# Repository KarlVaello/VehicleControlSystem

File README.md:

# Vehicle Control System

### What is VCS?
In modern vehicles almost 80% of the vehicle is controlled electronically. That's just VCS, a control system. Focused on electric vehicles but can be easily modified for other types.
VCS consists of several units and modules, all connected by an area network bus, based on rs-485 and my own [data protocol](https://github.com/KarlVaello/VCS/wiki/Unit-Communication-protocol), allowing modularization.
In this project you will find both the hardware and the software of each unit or module.

 Electronic control units / modules
 
UNITS:
- CCU Central Control Unit
	- CCU Cluster Control Unit
	- CCU Central Control Unit
- EmCU Electric-motor Control Unit
- BCU Battery Control Unit

MODULES:
- CcCM Central-console Control Module
- SteeringWheel Control Module
- BCM Body Control Module
- BlCM Back-lights Control Module
- FlCM Front-lights Control Module

### SCREENSHOTS

BASE MODULE

# Full Documentation

See the [WIKI](https://github.com/KarlVaello/VCS/wiki) for full documentation, examples, operational details and other information.

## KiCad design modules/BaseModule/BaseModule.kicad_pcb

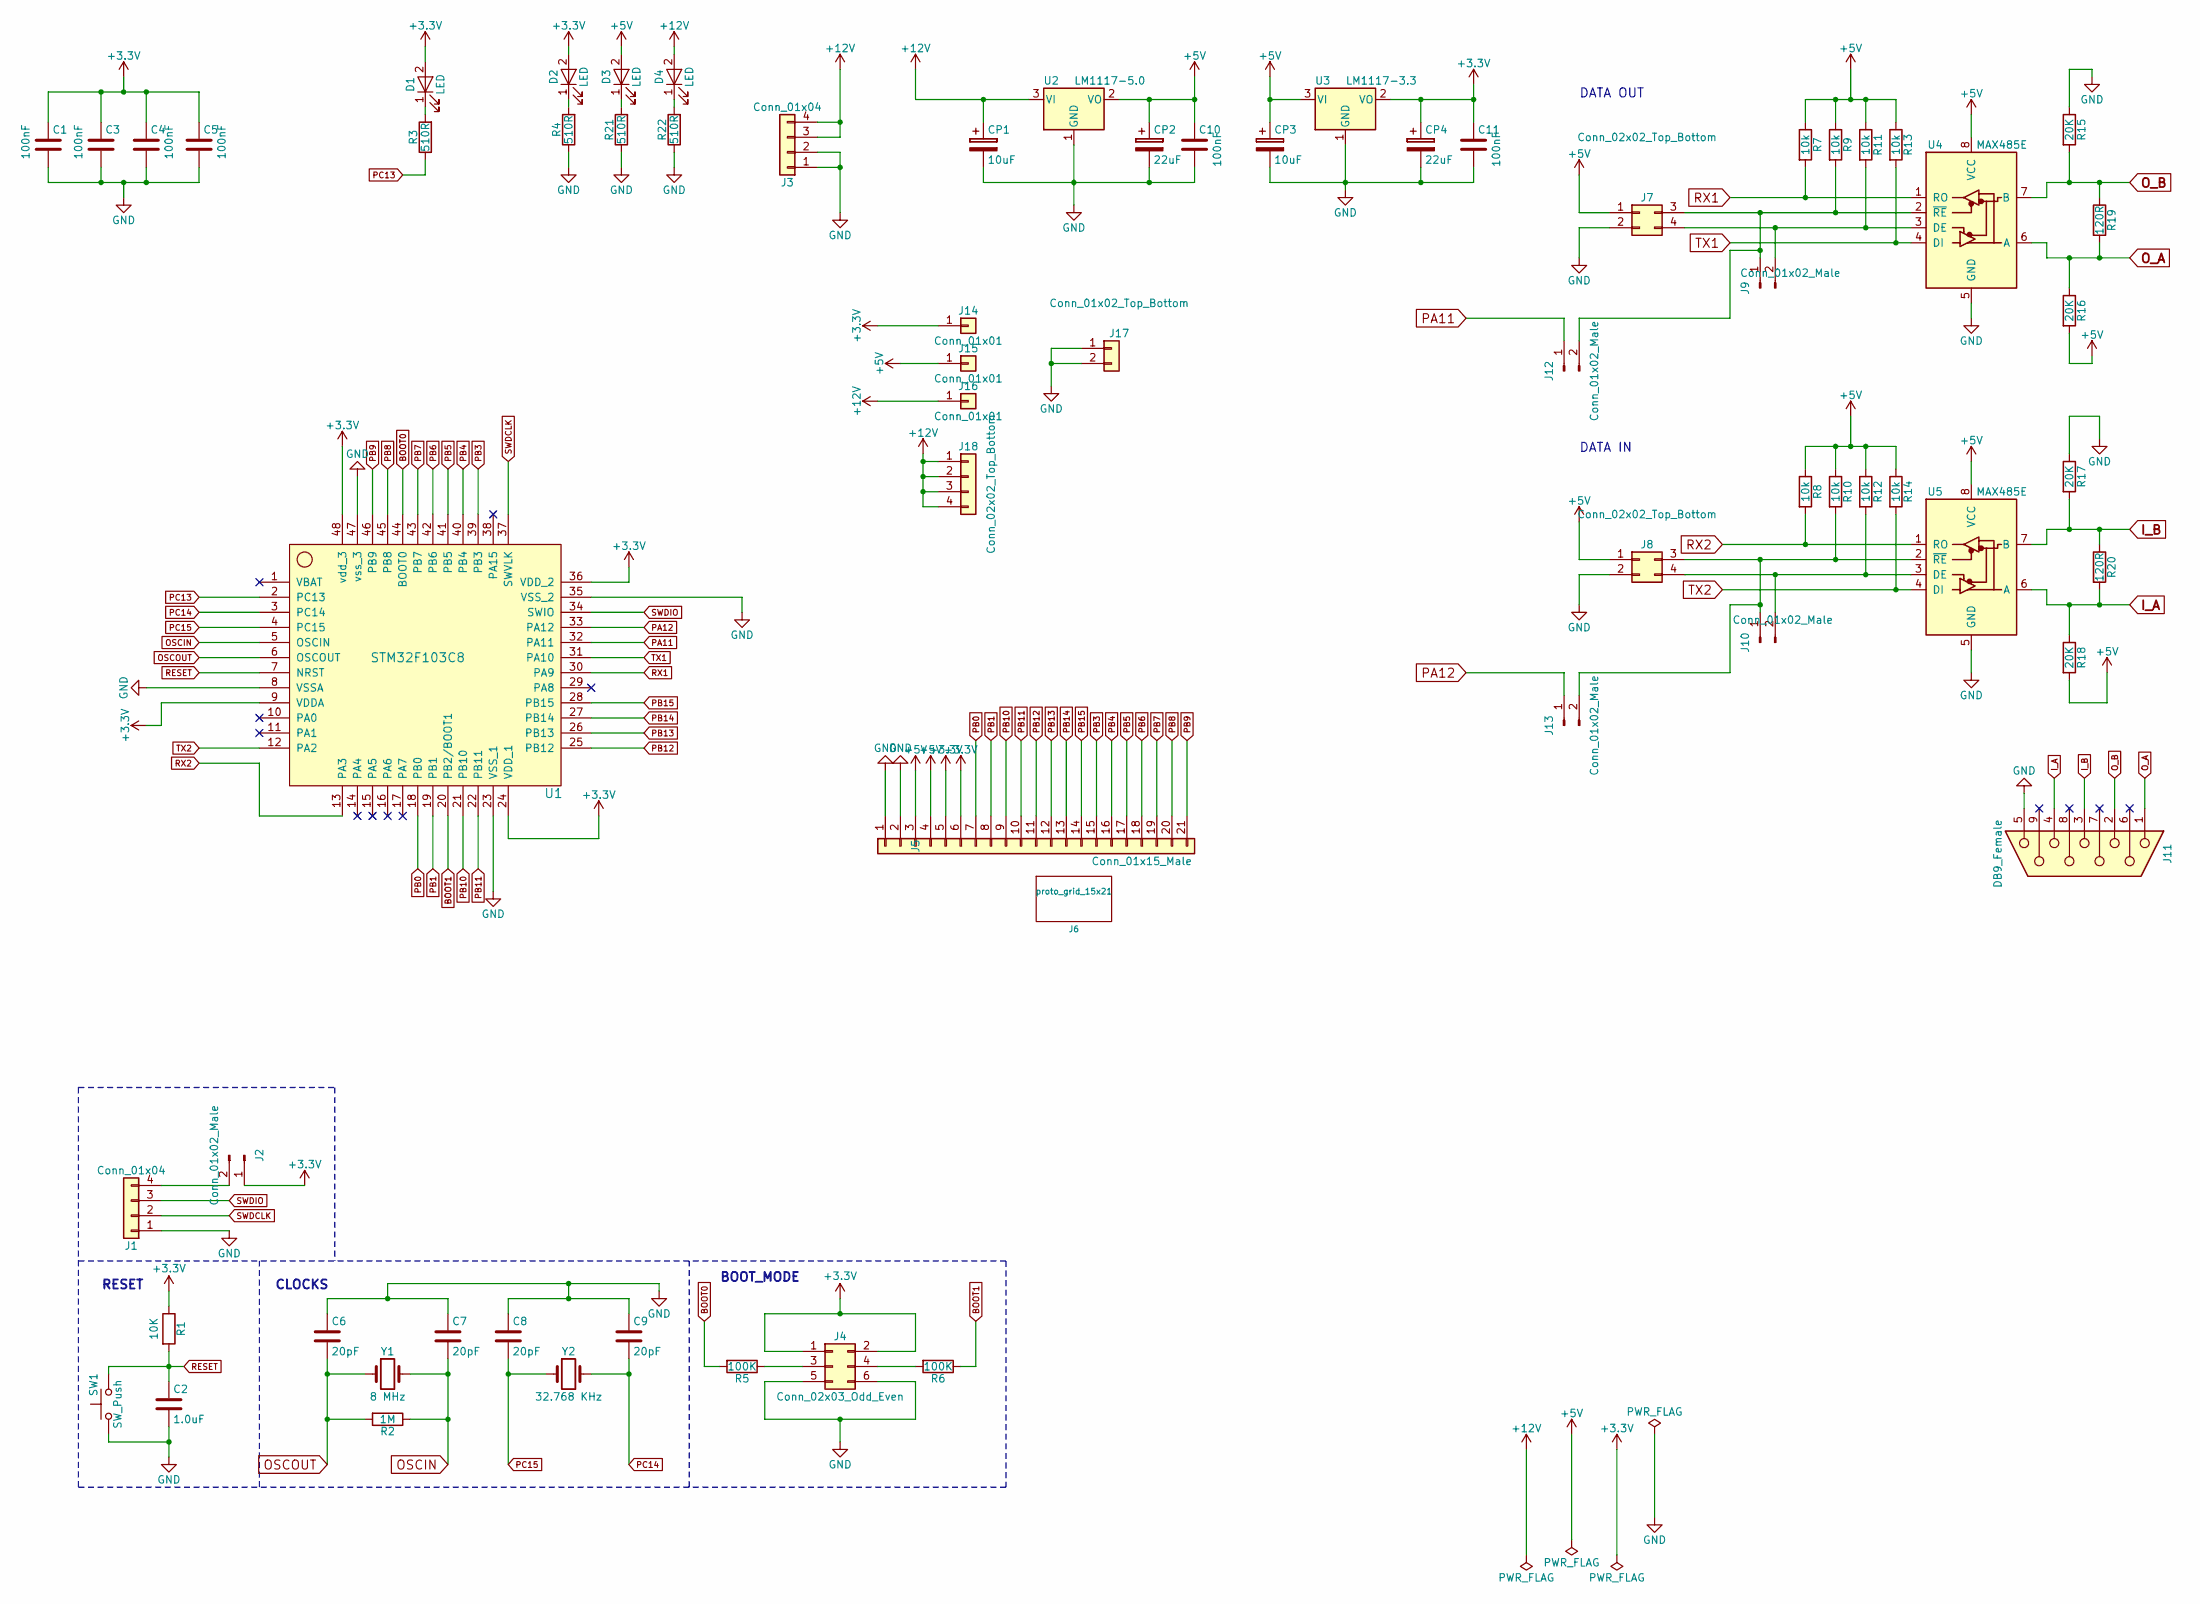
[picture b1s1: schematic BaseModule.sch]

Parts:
C1, C3, C4, C5: 100nF; C_0603_HandSoldering
C2: 1.0uF; C_0603_HandSoldering
C6, C7, C8, C9: 20pF; C_0603_HandSoldering
C10, C11: 100nF; C_0805_HandSoldering
CP1, CP3: 10uF; CP_Tantalum_Case-B_EIA-3528-21_Hand
CP2, CP4: 22uF; CP_Tantalum_Case-B_EIA-3528-21_Hand
D1, D2, D3, D4: LED; LED_0805_HandSoldering
J1: Conn_01x04; Pin_Header_Straight_1x04_Pitch2.54mm
J2, J9, J10, J12, J13: Conn_01x02_Male; Pin_Header_Straight_1x02_Pitch2.54mm
J3: Conn_01x04; Molex_MiniFit-JR-5569-04A2_2x02x4.20mm_Angled
J4: Conn_02x03_Odd_Even; Pin_Header_Straight_2x03_Pitch2.54mm
J5: Conn_01x15_Male; Socket_Strip_Straight_1x21_Pitch2.54mm
J6: proto_grid_15x21; grid
J7, J8: Conn_02x02_Top_Bottom; Pin_Header_Straight_2x02_Pitch2.54mm
J11: DB9_Female
J14, J15, J16: Conn_01x01; Pin_Header_Straight_1x01_Pitch2.54mm
J17: Conn_01x02_Top_Bottom; Pin_Header_Straight_1x02_Pitch2.54mm
J18: Conn_02x02_Top_Bottom; Socket_Strip_Straight_1x04_Pitch2.54mm
R1: 10K; R_0603_HandSoldering
R2: 1M; R_0603_HandSoldering
R3, R4, R21, R22: 510R; R_0603_HandSoldering
R5, R6: 100K; R_0603_HandSoldering
R7, R8, R9, R10, R11, R12, R13, R14: 10k; R_0603_HandSoldering
R15, R16, R17, R18: 20K; R_0603_HandSoldering
R19, R20: 120R; R_0603_HandSoldering
SW1: SW_Push; SW_PUSH_6mm_h8.5mm
U1: STM32F103C8; LQFP-48_7x7mm_Pitch0.5mm
U2: LM1117-5.0; SOT-223
U3: LM1117-3.3; SOT-223
U4, U5: MAX485E; SOIC-8_3.9x4.9mm_Pitch1.27mm
Y1: 8 MHz; Crystal_HC49-4H_Vertical
Y2: 32.768 KHz; Crystal_SMD_SeikoEpson_MC306-4pin_8.0x3.2mm_HandSoldering

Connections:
+3V3: C1.1, C3.1, C4.1, C5.1, C11.1, CP4.1, D1.2 (A), D2.2 (A), J2.1, J4.1, J4.2, J5.5, J5.6, J14.1, R1.1, U1.9 (VDDA), U1.24 (VDD_1), U1.36 (VDD_2), U1.48 (vdd_3), U3.2 (VO)
+5V: C10.1, CP2.1, CP3.1, D3.2 (A), J5.3, J5.4, J7.1, J8.1, J15.1, R7.1, R8.1, R9.1, R10.1, R11.1, R12.1, R13.1, R14.1, R16.2, R18.2, U2.2 (VO), U3.3 (VI), U4.8 (VCC), U5.8 (VCC)
+12V: CP1.1, D4.2 (A), J3.3, J3.4, J16.1, J18.1, J18.2, J18.3, J18.4, U2.3 (VI)
BOOT0: R5.2, U1.44 (BOOT0)
BOOT1: R6.1, U1.20 (PB2/BOOT1)
GND: C1.2, C2.2, C3.2, C4.2, C5.2, C6.1, C7.1, C8.1, C9.1, C10.2, C11.2, CP1.2, CP2.2, CP3.2, CP4.2, J1.1, J3.1, J3.2, J4.5, J4.6, J5.1, J5.2, J7.2, J8.2, J11.5, J17.1, J17.2, R4.1, R15.1, R17.1, R21.1, R22.1, SW1.1, U1.8 (VSSA), U1.23 (VSS_1), U1.35 (VSS_2), U1.47 (vss_3), U2.1 (GND), U3.1 (GND), U4.5 (GND), U5.5 (GND)
I_A: J11.4, R18.1, R20.2, U5.6 (A)
I_B: J11.3, R17.2, R20.1, U5.7 (B)
unnamed: D1.1 (K), R3.2
unnamed: D2.1 (K), R4.2
unnamed: D3.1 (K), R21.2
unnamed: D4.1 (K), R22.2
unnamed: J1.4, J2.2
unnamed: J4.3, R5.1
unnamed: J4.4, R6.2
unnamed: J7.4, J9.2, R11.2, U4.3 (DE)
unnamed: J8.3, J10.1, J13.2, R10.2, U5.2 (~RE)
unnamed: J8.4, J10.2, R12.2, U5.3 (DE)
unnamed: J7.3, J9.1, J12.2, R9.2, U4.2 (~RE)
OSCIN: C7.2, R2.1, U1.5 (OSCIN), Y1.2
OSCOUT: C6.2, R2.2, U1.6 (OSCOUT), Y1.1
O_A: J11.1, R16.1, R19.2, U4.6 (A)
O_B: J11.2, R15.2, R19.1, U4.7 (B)
PA11: J12.1, U1.32 (PA11)
PA12: J13.1, U1.33 (PA12)
PB0: J5.7, U1.18 (PB0)
PB1: J5.8, U1.19 (PB1)
PB3: J5.15, U1.39 (PB3)
PB4: J5.16, U1.40 (PB4)
PB5: J5.17, U1.41 (PB5)
PB6: J5.18, U1.42 (PB6)
PB7: J5.19, U1.43 (PB7)
PB8: J5.20, U1.45 (PB8~)
PB9: J5.21, U1.46 (PB9)
PB10: J5.9, U1.21 (PB10)
PB11: J5.10, U1.22 (PB11)
PB12: J5.11, U1.25 (PB12)
PB13: J5.12, U1.26 (PB13)
PB14: J5.13, U1.27 (PB14)
PB15: J5.14, U1.28 (PB15)
PC13: R3.1, U1.2 (PC13)
PC14: C9.2, U1.3 (PC14), Y2.2
PC15: C8.2, U1.4 (PC15), Y2.1
RESET: C2.1, R1.2, SW1.2, U1.7 (NRST)
RX1: R7.2, U1.30 (PA9), U4.1 (RO)
RX2: R8.2, U1.13 (PA3), U5.1 (RO)
SWDCLK: J1.2, U1.37 (SWVLK)
SWDIO: J1.3, U1.34 (SWIO)
TX1: R13.2, U1.31 (PA10), U4.4 (DI)
TX2: R14.2, U1.12 (PA2), U5.4 (DI)

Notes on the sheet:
DATA OUT
DATA IN
RESET
CLOCKS
BOOT_MODE

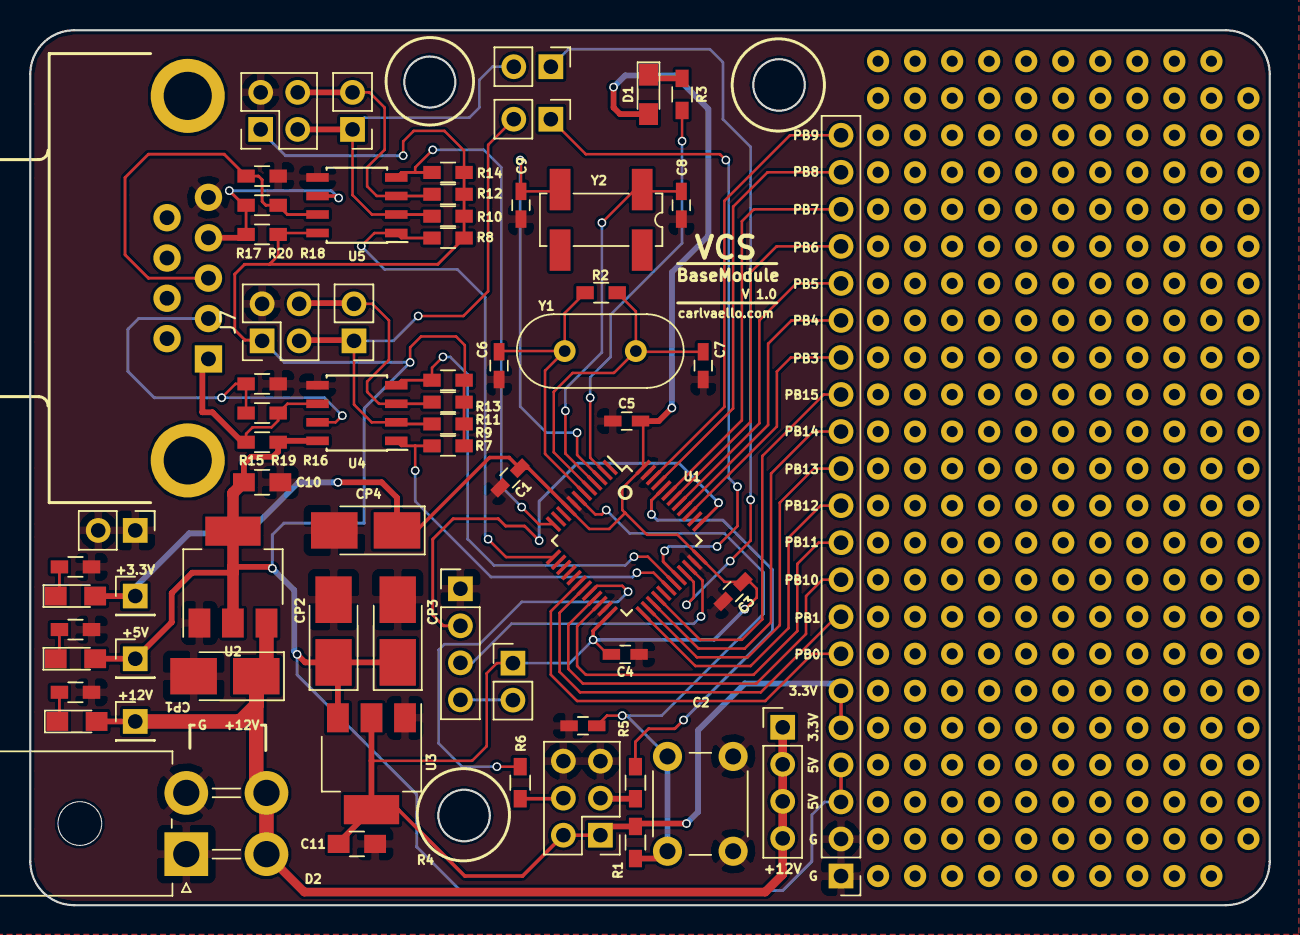
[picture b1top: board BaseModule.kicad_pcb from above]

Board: 2 copper layers, 85.0 x 60.0 mm, 67 parts (0 on the bottom side), 50 nets.

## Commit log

2017-02-07 Initial commit
    Initial commit
2017-02-08 Basic Serial Implementation
    Basic Serial Implementation
2017-02-08 Migrated widgets to new display widget system
    Migrated all widget to paintEvent and QpainterS
    Added new errorIcon.
    Corrected speedPinter display
2017-02-08 Serial communication updates
    Serial communication updates
2017-02-09 More paintEvent migration
    More paintEvent migration
2017-02-10 Font, serial and qprinter modifications
    Font, serial and qprinter modifications
2017-02-10 New Screen size (pixels)
    New Screen size (pixels)
2017-02-15 New Fonts
2017-02-16 readme file, new serial class (UpdateSerial.py)
2017-02-16 readme update
2017-02-16 readme updates
2017-02-17 more readme updates
2017-02-17 Update README.md
    More readme updates
2017-02-17 Folders modifications
    Folders, descriptions modifications to add Order to Project
2017-02-17 Adding more project info
    Adding more project info
2017-02-17 More info, files ranaming
    More info, files ranaming
2017-02-17 more info
2017-02-20 new classes
2017-02-20 new classes files
2017-02-20 New SVG files
    New SVG files to get better rendering UI
2017-02-20 New angle correction speedPointer
    New angle correction speedPointer
2017-02-20 Added test sounds
    Added test sounds
2017-02-21 try to add some sound
2017-02-21 New Cluster Display size 1280x720 to fit SHARP TFT-LCD LQ123K1LG03
2017-02-21 Minor changes
2017-02-21 Minor changes. Wiring diagram update
    Minor changes. Wiring diagram update
2017-02-22 New Icon to test Qthread
2017-02-23 Graphics update
    Graphics update
2017-02-23 minus modifications
2017-02-23 Minimal changes + Screenshot
    Minimal changes + Screenshot
2017-02-24 Icongs and more screenshots
    Icongs and more screenshots
2017-02-24 Set theme jekyll-theme-dinky
2017-02-24 Set theme jekyll-theme-slate
2017-02-25 New TODO file
2017-02-25 WiringDiagram.xml
2017-02-25 WiringDiagram.png
2017-02-25 Wiring diagram update
    Wiring diagram update
2017-02-26 Update WiringDiagram
2017-02-26 new wiringdiagram
2017-02-26 New EmCU folder and KiCad projecto
    New EmCU folder and KiCad projecto
2017-02-27 STM32 Documentation. STM32 Core board update
2017-03-01 Graphics update
2017-03-10 Cluster display info docs
2017-03-20 graphic update
2017-03-20 folders mooving and renamings
2017-03-20 Update to QT c++ project
    Update to QT c++ project to get better performance
2017-03-21 Link img files by resources on QT
2017-03-21 minimal updates
2017-03-22 Starting to implement notification systema
2017-03-22 notifications updates
2017-03-23 Notifications works
    Basic notifications works
    NotificationInfo
    NotificationManager
    NotificationWidget
    NotificationWidgetManage
2017-03-24 notification updates
2017-04-04 New Classes to communicate between units
    New UnitCommunication class, data exchange.
    New Infotainment class, data holder.
    More info on the wiki.
    cameraCaptureBuffer and cameraSteam are new too but there are on a
    standby because it’s need a specific hardware (camera) selection to
    continue develop it. The hardware determines almost all code work.
2017-04-04 Unit Communication diagram
2017-04-04 minimal update
2017-04-04 min updates
2017-04-04 data infotaiment updates
2017-04-05 update smooth speed pointer rotation
2017-04-05 debug communication error
2017-04-05 unitCommunication optimization routines and varaibles
2017-04-18 RS485 network on receiving data working perfect
2017-05-13 folders reorganized, arduino stm32 code rs-485 for test communications
2017-05-16 unit communication updates
2017-05-19 communication updates
2017-05-24 DB9 connector
2017-05-24 DB9_SINGLE connector
2017-05-25 DB9_single updated
2017-05-25 new db9 single stl
2017-06-27 Added Base module
    Added Base Module as de base circuit of every module with stm32
    microcontroller
2017-06-28 BaseBoard updates + hardware documentation
2017-07-07 base module update
    base module update
2017-07-07 gitignore
    gitignore
2017-07-07 UnitCommunication updates
    UnitCommunication updates
2017-07-10 unitCommunication_diagram Update
2017-07-16 unitCommunication Updates
    Now unitCommunication just hold diferente communication (propulsion,
    confort…). Even different communication had their own new class. The
    just manage their own communication and in different threats.
2017-07-16 documentation and base module updates
2017-07-17 Documentation update
2017-07-19 Updates unitPropulsionCom + graphics
    unitPropulsionCommunication works perfect right now tested with modules
    as emitters.
2017-08-02 BaseModule pcb updates
2017-09-13 Minimal updates on cluster.cpp
2017-09-13 Updates on .pro user settings
2017-09-13 Rename notificationmanager.h to notificationManager.h
2017-09-13 Rename notificationinfo.cpp to notificationInfo.cpp
2017-09-13 Rename notificationinfo.h to notificationInfo.h
2017-09-13 Rename notificationmanager.cpp to notificationManager.cpp
2017-09-13 Rename notificationwidget.cpp to notificationWidget.cpp
2017-09-13 Rename notificationwidget.h to notificationWidget.h
2017-09-14 Project clean for Linux
2017-09-14 Add font
2017-10-24 BaseModule updates (new board)
    Made with kicad
2017-10-26 BaseModule updates and documentation updates
2017-10-27 BaseModule ScreenShoot update
